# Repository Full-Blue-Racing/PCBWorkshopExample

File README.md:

# PCBWorkshopExample

Example schematic and PCB design for a basic ESP32 PCB, with CAN connection.

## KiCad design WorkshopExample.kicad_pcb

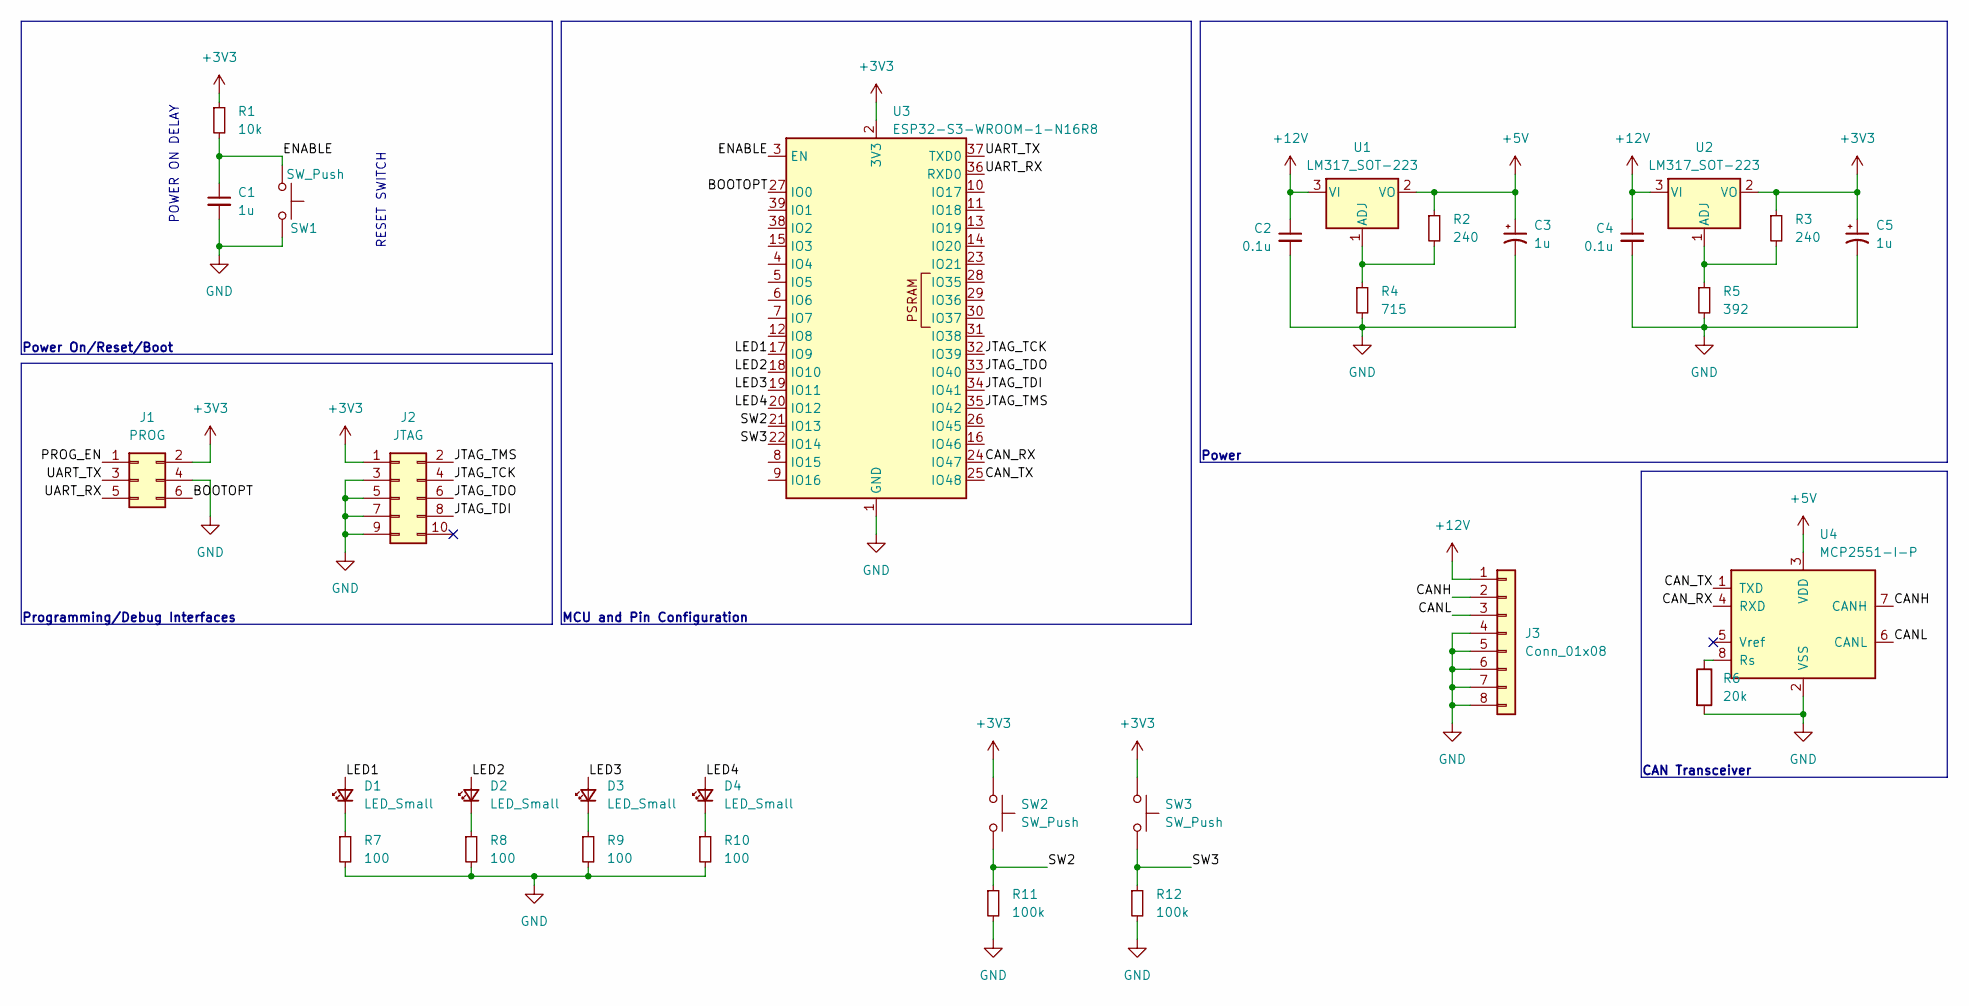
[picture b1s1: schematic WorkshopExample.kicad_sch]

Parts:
C1, C3, C5: 1u; C_Disc_D5.0mm_W2.5mm_P2.50mm
C2, C4: 0.1u; C_Disc_D5.0mm_W2.5mm_P2.50mm
D1, D2, D3, D4: LED_Small; LED_D5.0mm
J1: PROG; PinSocket_2x03_P2.54mm_Vertical
J2: JTAG; PinSocket_2x05_P2.54mm_Vertical
J3: Conn_01x08; TE_776280-1
R1: 10k; R_Axial_DIN0207_L6.3mm_D2.5mm_P10.16mm_Horizontal
R2, R3: 240; R_Axial_DIN0207_L6.3mm_D2.5mm_P10.16mm_Horizontal
R4: 715; R_Axial_DIN0207_L6.3mm_D2.5mm_P10.16mm_Horizontal
R5: 392; R_Axial_DIN0207_L6.3mm_D2.5mm_P10.16mm_Horizontal
R6: 20k; R_Axial_DIN0207_L6.3mm_D2.5mm_P10.16mm_Horizontal
R7, R8, R9, R10: 100; R_Axial_DIN0207_L6.3mm_D2.5mm_P10.16mm_Horizontal
R11, R12: 100k; R_Axial_DIN0207_L6.3mm_D2.5mm_P10.16mm_Horizontal
SW1, SW2, SW3: SW_Push; SW_PUSH_1P1T_6x3.5mm_H4.3_APEM_MJTP1243
U1, U2: LM317_SOT-223; SOT-223-3_TabPin2
U3: ESP32-S3-WROOM-1-N16R8; ESP32-S3-WROOM-1
U4: MCP2551-I-P; DIP-8_W7.62mm

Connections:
+3V3: C5.1, J1.2, J2.1, R1.1, R3.1, SW2.1, SW3.1, U2.2 (VO), U3.2 (3V3)
+5V: C3.1, R2.1, U1.2 (VO), U4.3 (VDD)
+12V: C2.1, C4.1, J3.1, U1.3 (VI), U2.3 (VI)
/BOOTOPT: J1.6, U3.27 (IO0)
/CANH: J3.2, U4.7 (CANH)
/CANL: J3.3, U4.6 (CANL)
/CAN_RX: U3.24 (IO47), U4.4 (RXD)
/CAN_TX: U3.25 (IO48), U4.1 (TXD)
/ENABLE: C1.1, R1.2, SW1.1, U3.3 (EN)
/JTAG_TCK: J2.4, U3.32 (IO39)
/JTAG_TDI: J2.8, U3.34 (IO41)
/JTAG_TDO: J2.6, U3.33 (IO40)
/JTAG_TMS: J2.2, U3.35 (IO42)
/LED1: D1.2 (A), U3.17 (IO9)
/LED2: D2.2 (A), U3.18 (IO10)
/LED3: D3.2 (A), U3.19 (IO11)
/LED4: D4.2 (A), U3.20 (IO12)
/PROG_EN: J1.1
/SW2: R11.1, SW2.2, U3.21 (IO13)
/SW3: R12.1, SW3.2, U3.22 (IO14)
/UART_RX: J1.5, U3.36 (RXD0)
/UART_TX: J1.3, U3.37 (TXD0)
GND: C1.2, C2.2, C3.2, C4.2, C5.2, J1.4, J2.3, J2.5, J2.7, J2.9, J3.4, J3.5, J3.6, J3.7, J3.8, R4.2, R5.2, R6.2, R7.2, R8.2, R9.2, R10.2, R11.2, R12.2, SW1.2, U3.1 (GND), U3.40 (GND), U3.41 (GND), U4.2 (VSS)
unnamed: D1.1 (K), R7.1
unnamed: D2.1 (K), R8.1
unnamed: D3.1 (K), R9.1
unnamed: D4.1 (K), R10.1
unnamed: R2.2, R4.1, U1.1 (ADJ)
unnamed: R3.2, R5.1, U2.1 (ADJ)
unnamed: R6.1, U4.8 (Rs)

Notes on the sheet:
Programming/Debug Interfaces
Power
Power On/Reset/Boot
RESET SWITCH
POWER ON DELAY
MCU and Pin Configuration
CAN Transceiver

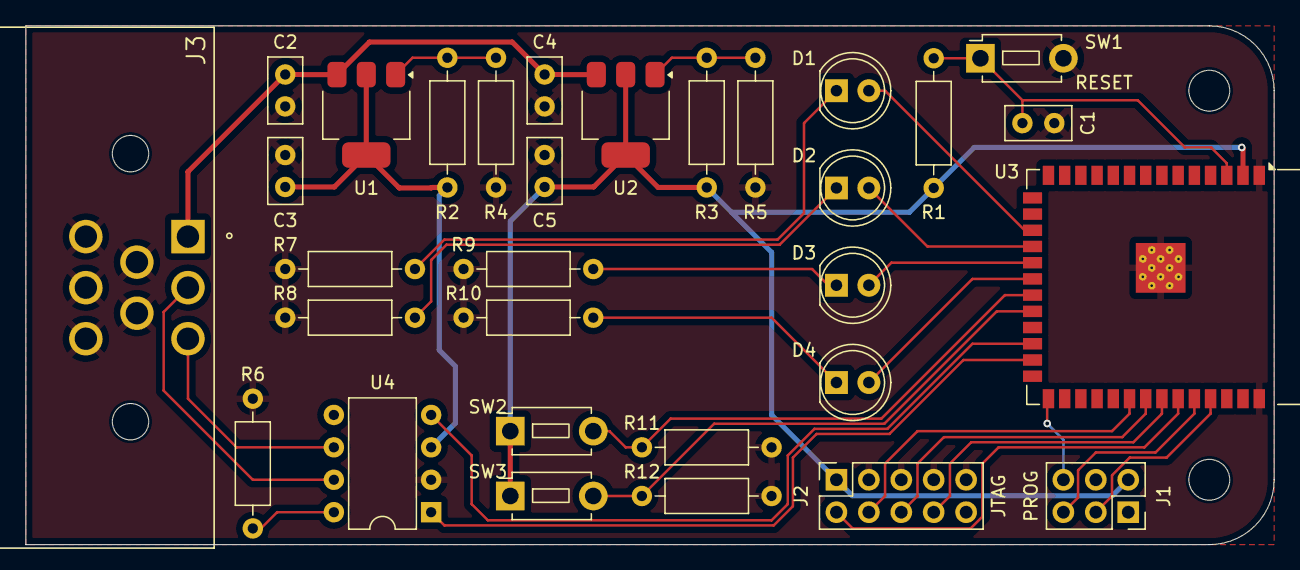
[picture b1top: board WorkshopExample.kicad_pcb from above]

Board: 2 copper layers, 97.8 x 40.6 mm, 31 parts (0 on the bottom side), 29 nets.

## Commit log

2024-11-19 Complete Example Schematic and PCB
2024-11-19 Update Gerber Export Settings
